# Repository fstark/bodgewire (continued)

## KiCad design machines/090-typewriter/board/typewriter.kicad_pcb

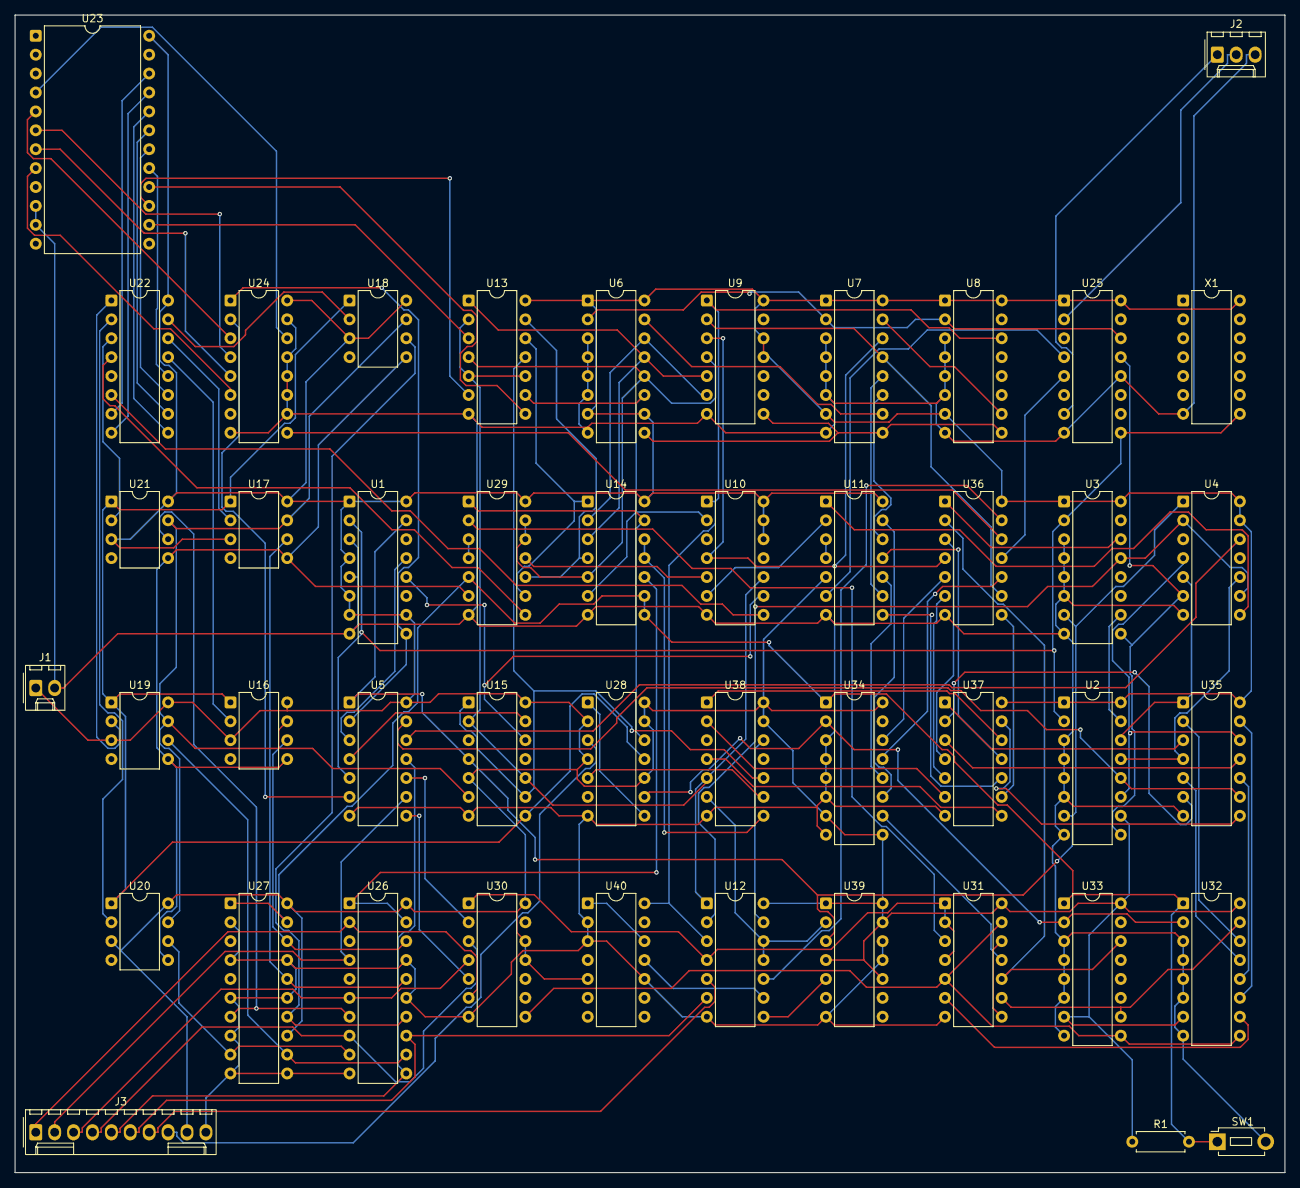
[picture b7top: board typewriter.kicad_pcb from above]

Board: 2 copper layers, 170.6 x 155.5 mm, 46 parts (0 on the bottom side), 127 nets.

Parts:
J1: POWER; Molex_KK-254_AE-6410-02A_1x02_P2.54mm_Vertical
J2: VIDEO; Molex_KK-254_AE-6410-03A_1x03_P2.54mm_Vertical
J3: KEYBOARD; Molex_KK-254_AE-6410-10A_1x10_P2.54mm_Vertical
R1: 4k7; R_Axial_DIN0207_L6.3mm_D2.5mm_P7.62mm_Horizontal
SW1: BUTTON; SW_PUSH_1P1T_6x3.5mm_H5.0_APEM_MJTP1250
U1, U2, U3, U6, U7, U8, U32, U33, U34: 74LS161; DIP-16_W7.62mm
U4, U10, U15, U38: 74LS20; DIP-14_W7.62mm
U5: 74LS04; DIP-14_W7.62mm
U9, U30: 74LS30; DIP-14_W7.62mm
U11, U35, U36: 74LS86; DIP-14_W7.62mm
U12, U14: 74LS02; DIP-14_W7.62mm
U13: 74LS08; DIP-14_W7.62mm
U16, U17, U18, U19, U20, U21: 2524; DIP-8_W7.62mm
U22: 2518; DIP-16_W7.62mm
U23: 2513; DIP-24_W15.24mm
U24: 74LS165; DIP-16_W7.62mm
U25: 74LS175; DIP-16_W7.62mm
U26, U27: 74LS244; DIP-20_W7.62mm
U28, U39: 74LS74; DIP-14_W7.62mm
U29, U31: 74LS00; DIP-14_W7.62mm
U37: 74LS27; DIP-14_W7.62mm
U40: 74LS93; DIP-14_W7.62mm
X1: OSC; DIP-14_W7.62mm

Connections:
ACTIVE: U10.10 (2B), U12.1 (1Y), U13.2 (1B), U13.5 (2B), U13.10 (3B), U15.2 (1B), U15.10 (2B), U38.5 (1D)
ADV: U31.6 (2Y), U32.10 (ENT)
B0: U22.12 (OUT1), U23.17 (A4)
B1: U22.11 (OUT2), U23.18 (A5)
B2: U22.10 (OUT3), U23.19 (A6)
B3: U22.9 (OUT4), U23.20 (A7)
B4: U22.8 (OUT5), U23.21 (A8)
B5: U22.7 (OUT6), U23.22 (A9)
BLINK: U12.9 (3B), U40.11 (QD)
C0: U2.14 (QA), U4.5 (1D), U35.1 (1A)
C1: U2.13 (QB), U4.10 (2B), U35.4 (2A)
C2: U2.12 (QC), U5.13 (6A), U35.9 (3A)
C2_N: U4.12 (2C), U5.12
C3: U2.11 (QD), U4.4 (1C), U35.12 (4A)
C4: U3.14 (QA), U36.1 (1A)
C5: U3.13 (QB), U4.2 (1B), U4.9 (2A), U12.2 (1A)
CC: U2.15 (RCO), U3.10 (ENT)
CLEAR: U14.10 (3Y), U26.1 (1OE_N), U26.19 (2OE_N)
CLEAR_N: R1.2, SW1.1, U14.8 (3A), U14.9 (3B), U27.1 (1OE_N), U27.19 (2OE_N), U29.5 (2B), U32.1 (CLR_N), U33.1 (CLR_N), U34.1 (CLR_N)
CLK: U1.2 (CLK), U2.2 (CLK), U3.2 (CLK), U5.5 (3A), U25.9 (CLK), X1.8 (OUT)
CLK_N: U5.6 (3Y), U24.2 (CLK)
CR_N: U30.8 (Y), U31.5 (2B), U31.13 (4B), U32.9 (LOAD_N), U33.9 (LOAD_N)
CTL: U12.4 (2Y), U30.1 (A), U31.1 (1A), U31.2 (1B), U31.4 (2A)
CURSOR_N: U12.8 (3A), U39.5 (1Q)
CUR_SHOW: U12.10 (3Y), U36.13 (4B)
D0: J3.1 (D0), U26.2 (1A1), U30.6 (F)
D1: J3.2 (D1), U5.9 (4A), U26.4 (1A2)
D1_N: U5.8 (4Y), U30.5 (E)
D2: J3.3 (D2), U26.6 (1A3), U30.4 (D)
D3: J3.4 (D3), U26.8 (1A4), U30.3 (C)
D4: J3.5 (D4), U5.11 (5A), U26.11 (2A1)
D4_N: U5.10 (5Y), U30.2 (B)
D5: J3.6 (D5), U12.6 (2B), U26.13 (2A2)
D6: J3.7 (D6), U12.5 (2A)
DOT_END: U1.15 (RCO), U2.7 (ENP), U3.7 (ENP), U4.1 (1A), U5.1 (1A), U15.4 (1C), U39.3 (1CLK)
DOT_LOAD_N: U1.9 (LOAD_N), U5.2 (1Y), U24.1 (SH_LD_N)
EQ0: U37.12 (1Y), U38.1 (1A)
EQ1: U37.6 (2Y), U38.2 (1B)
EQ2: U37.8 (3Y), U38.4 (1C)
F1: U23.4 (O1), U24.14 (D)
F2: U23.5 (O2), U24.3 (E)
F3: U23.6 (O3), U24.4 (F)
F4: U23.7 (O4), U24.5 (G)
F5: U23.8 (O5), U24.6 (H)
FRAME2: U40.1 (CKB), U40.12 (QA)
FRAME_END_N: U6.9 (LOAD_N), U7.9 (LOAD_N), U8.9 (LOAD_N), U9.8 (Y)
GL1: U13.3 (1Y), U23.14 (A1)
GL2: U13.6 (2Y), U23.15 (A2)
GL3: U13.8 (3Y), U23.16 (A3)
GND: J1.2 (GND), J2.3 (GND), J3.10 (GND), SW1.2, U1.3 (A), U1.5 (C), U1.8 (GND), U2.3 (A), U2.4 (B), U2.5 (C), U2.6 (D), U2.8 (GND), U3.3 (A), U3.4 (B), U3.5 (C), U3.6 (D), U3.8 (GND), U4.7 (GND), U5.7 (GND), U6.3 (A), U6.4 (B), U6.5 (C), U6.6 (D), U6.8 (GND), U7.3 (A), U7.4 (B), U7.5 (C), U7.6 (D), U7.8 (GND), U8.3 (A), U8.4 (B), U8.5 (C), U8.6 (D), U8.8 (GND), U9.7 (GND), U10.7 (GND), U11.7 (GND), U12.7 (GND), U13.7 (GND), U14.7 (GND), U15.7 (GND), U23.10 (GND), U23.11 (CE_N), U24.8 (GND), U24.10 (SER), U24.11 (A), U24.12 (B), U24.13 (C), U24.15 (CLK_INH), U25.8 (GND), U25.12 (3D), U26.10 (GND), U26.15 (2A3), U26.17 (2A4), U27.2 (1A1), U27.4 (1A2), U27.6 (1A3), U27.8 (1A4), U27.10 (GND), U27.11 (2A1), U27.15 (2A3), U27.17 (2A4), U28.7 (GND), U29.7 (GND), U30.7 (GND), U31.7 (GND), U32.3 (A), U32.4 (B), U32.5 (C), U32.6 (D), U32.8 (GND), U33.3 (A), U33.4 (B), U33.5 (C), U33.6 (D), U33.8 (GND), U34.3 (A), U34.4 (B), U34.5 (C), U34.6 (D), U34.8 (GND), U35.7 (GND), U36.7 (GND), U37.7 (GND), U38.7 (GND), U39.7 (GND), U39.11 (2CLK), U39.12 (2D), U40.2 (R01), U40.3 (R02), U40.10 (GND), X1.7 (GND)
GO: U14.13 (4Y), U28.12 (2D), U29.1 (1A)
GO_N: U14.11 (4A), U14.12 (4B), U38.8 (2Y)
HSYNC_N: U4.8 (2Y), U11.1 (1A)
KEY: U28.5 (1Q), U38.9 (2A)
LINE_END: U6.2 (CLK), U7.2 (CLK), U8.2 (CLK), U25.14 (4Q_N)
LINE_END_N: U2.9 (LOAD_N), U3.9 (LOAD_N), U4.6 (1Y), U25.13 (4D)
MATCH: U12.13 (4Y), U38.12 (2C)
MATCH_N: U12.11 (4A), U12.12 (4B), U38.6 (1Y), U39.2 (1D)
NE0: U35.3 (1Y), U37.1 (1A)
NE1: U35.6 (2Y), U37.2 (1B)
NE2: U35.8 (3Y), U37.13 (1C)
NE3: U35.11 (4Y), U37.3 (2A)
NE4: U36.3 (1Y), U37.4 (2B)
NE5: U36.6 (2Y), U37.5 (2C)
NE6: U36.8 (3Y), U37.9 (3A)
NE7: U11.8 (3Y), U37.10 (3B)
NE8: U11.11 (4Y), U37.11 (3C)
P0: U16.2 (OUT), U22.13 (IN1)
P1: U17.2 (OUT), U22.14 (IN2)
P2: U18.2 (OUT), U22.15 (IN3)
P3: U19.2 (OUT), U22.1 (IN4)
P4: U20.2 (OUT), U22.2 (IN5)
P5: U21.2 (OUT), U22.3 (IN6)
PHI1_N: U15.6 (1Y), U16.7 (PHI1), U17.7 (PHI1), U18.7 (PHI1), U19.7 (PHI1), U20.7 (PHI1), U21.7 (PHI1)
PHI2_N: U15.8 (2Y), U16.1 (PHI2), U17.1 (PHI2), U18.1 (PHI2), U19.1 (PHI2), U20.1 (PHI2), U21.1 (PHI2), U28.11 (2CLK)
PRINT: U29.2 (1B), U31.3 (1Y)
QB: U1.13 (QB), U5.3 (2A)
QB_N: U5.4 (2Y), U15.13 (2D)
QC: U1.12 (QC), U10.9 (2A), U15.12 (2C)
ROW_CLK: U10.8 (2Y), U22.6 (CLK)
ROW_LOAD_N: U22.4 (REC), U29.8 (3Y)
ROW_TOP: U13.11 (4Y), U15.1 (1A), U15.9 (2A), U38.10 (2B)
STROBE: J3.8 (STROBE), U28.3 (1CLK)
SYNC: U11.3 (1Y), U11.4 (2A)
SYNC_N: J2.2 (SYNC_N), U25.2 (1Q)
SYNC_N_D: U11.6 (2Y), U25.4 (1D)
V0: U6.14 (QA), U9.6 (F), U14.2 (1A)
V1: U6.13 (QB), U9.5 (E), U13.1 (1A), U14.3 (1B)
V01_ZERO: U13.12 (4A), U14.1 (1Y), U29.9 (3A)
V2: U6.12 (QC), U9.4 (D), U13.4 (2A), U14.5 (2A), U29.12 (4A), U29.13 (4B)
V2_N: U10.5 (1D), U29.11
V3: U6.11 (QD), U10.2 (1B), U13.9 (3A), U14.6 (2B)
V4: U7.14 (QA), U9.3 (C), U10.4 (1C), U36.4 (2A)
V5: U7.13 (QB), U9.2 (B), U36.9 (3A)
V6: U7.12 (QC), U11.9 (3A)
V7: U7.11 (QD), U11.12 (4A)
V8: U8.14 (QA), U9.1 (A), U10.1 (1A), U12.3 (1B), U40.14 (CKA)
V23_ZERO: U13.13 (4B), U14.4 (2Y), U29.10 (3B)
VC1: U6.15 (RCO), U7.10 (ENT)
VC2: U7.15 (RCO), U8.10 (ENT)
VCC: J1.1 (VCC), J3.9 (VCC), R1.1, U1.1 (CLR_N), U1.4 (B), U1.6 (D), U1.7 (ENP), U1.10 (ENT), U1.16 (VCC), U2.1 (CLR_N), U2.10 (ENT), U2.16 (VCC), U3.1 (CLR_N), U3.16 (VCC), U4.13 (2D), U4.14 (VCC), U5.14 (VCC), U6.1 (CLR_N), U6.7 (ENP), U6.10 (ENT), U6.16 (VCC), U7.1 (CLR_N), U7.7 (ENP), U7.16 (VCC), U8.1 (CLR_N), U8.7 (ENP), U8.16 (VCC), U9.11 (G), U9.12 (H), U9.14 (VCC), U10.12 (2C), U10.13 (2D), U10.14 (VCC), U11.5 (2B), U11.14 (VCC), U12.14 (VCC), U13.14 (VCC), U14.14 (VCC), U15.5 (1D), U15.14 (VCC), U16.3 (READ), U16.8 (VCC), U17.3 (READ), U17.8 (VCC), U18.3 (READ), U18.8 (VCC), U19.3 (READ), U19.8 (VCC), U20.3 (READ), U20.8 (VCC), U21.3 (READ), U21.8 (VCC), U22.16 (VCC), U23.24 (VCC), U24.16 (VCC), U25.1 (CLR_N), U25.16 (VCC), U26.20 (VCC), U27.13 (2A2), U27.20 (VCC), U28.2 (1D), U28.4 (1PRE_N), U28.10 (2PRE_N), U28.13 (2CLR_N), U28.14 (VCC), U29.14 (VCC), U30.11 (G), U30.12 (H), U30.14 (VCC), U31.14 (VCC), U32.7 (ENP), U32.16 (VCC), U33.7 (ENP), U33.16 (VCC), U34.7 (ENP), U34.9 (LOAD_N), U34.16 (VCC), U35.14 (VCC), U36.14 (VCC), U37.14 (VCC), U38.13 (2D), U38.14 (VCC), U39.1 (1CLR_N), U39.4 (1PRE_N), U39.10 (2PRE_N), U39.13 (2CLR_N), U39.14 (VCC), U40.5 (VCC), X1.14 (VCC)
VIDEO: J2.1 (VIDEO), U25.7 (2Q)
VIDEO_D: U24.9 (QH), U36.12 (4A)
VIDEO_M: U25.5 (2D), U36.11 (4Y)
VSYNC_N: U10.6 (1Y), U11.2 (1B)
W0: U16.6 (IN), U26.18 (1Y1), U27.18 (1Y1)
W1: U17.6 (IN), U26.16 (1Y2), U27.16 (1Y2)
W2: U18.6 (IN), U26.14 (1Y3), U27.14 (1Y3)
W3: U19.6 (IN), U26.12 (1Y4), U27.12 (1Y4)
W4: U20.6 (IN), U26.9 (2Y1), U27.9 (2Y1)
W5: U21.6 (IN), U26.7 (2Y2), U27.7 (2Y2)
WR: U28.9 (2Q), U32.2 (CLK), U33.2 (CLK), U34.2 (CLK)
WRITE: U16.5 (WRITE), U17.5 (WRITE), U18.5 (WRITE), U19.5 (WRITE), U20.5 (WRITE), U21.5 (WRITE), U29.6 (2Y)
WRK_N: U29.3 (1Y), U29.4 (2A)
WR_N: U28.1 (1CLR_N), U28.8 (2Q_N)
X0: U32.14 (QA), U35.2 (1B)
X1: U32.13 (QB), U35.5 (2B)
X2: U32.12 (QC), U35.10 (3B)
X3: U32.11 (QD), U35.13 (4B)
X4: U31.10 (3B), U33.14 (QA), U36.2 (1B)
XC_N: U31.8 (3Y), U31.12 (4A)
XRCO: U31.9 (3A), U32.15 (RCO), U33.10 (ENT)
Y0: U34.14 (QA), U36.5 (2B)
Y1: U34.13 (QB), U36.10 (3B)
Y2: U11.10 (3B), U34.12 (QC)
Y3: U11.13 (4B), U34.11 (QD)
YEN: U31.11 (4Y), U34.10 (ENT)

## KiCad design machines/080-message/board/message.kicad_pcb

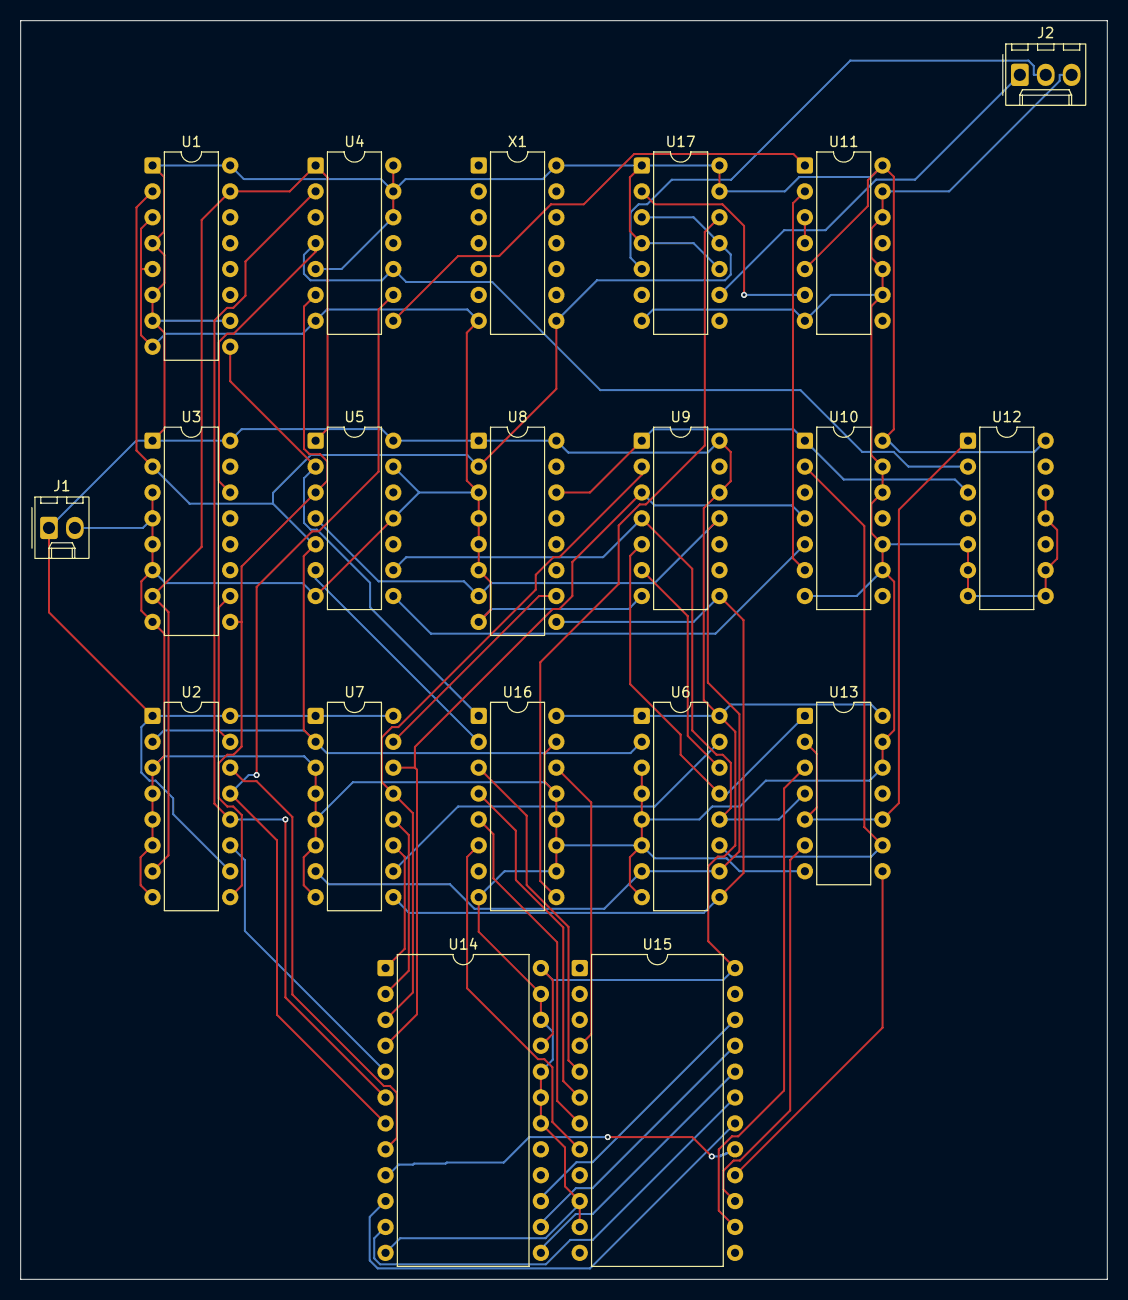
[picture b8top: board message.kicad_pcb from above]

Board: 2 copper layers, 106.6 x 123.5 mm, 20 parts (0 on the bottom side), 49 nets.

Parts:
J1: POWER; Molex_KK-254_AE-6410-02A_1x02_P2.54mm_Vertical
J2: VIDEO; Molex_KK-254_AE-6410-03A_1x03_P2.54mm_Vertical
U1, U2, U3, U6, U7, U8: 74LS161; DIP-16_W7.62mm
U4, U10: 74LS20; DIP-14_W7.62mm
U5: 74LS04; DIP-14_W7.62mm
U9: 74LS30; DIP-14_W7.62mm
U11: 74LS86; DIP-14_W7.62mm
U12: 74LS02; DIP-14_W7.62mm
U13: 74LS08; DIP-14_W7.62mm
U14: 2716; DIP-24_W15.24mm
U15: 2513; DIP-24_W15.24mm
U16: 74LS165; DIP-16_W7.62mm
U17: 74LS74; DIP-14_W7.62mm
X1: OSC; DIP-14_W7.62mm

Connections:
ACTIVE: U12.1 (1Y), U13.2 (1B), U13.5 (2B), U13.10 (3B)
C0: U2.14 (QA), U14.8 (A0)
C1: U2.13 (QB), U4.9 (2A), U14.7 (A1)
C2: U2.12 (QC), U4.2 (1B), U14.6 (A2)
C3: U2.11 (QD), U14.5 (A3)
C4: U3.14 (QA), U4.4 (1C), U4.10 (2B), U12.2 (1A)
CC: U2.15 (RCO), U3.10 (ENT)
CH0: U14.9 (O0), U15.17 (A4)
CH1: U14.10 (O1), U15.18 (A5)
CH2: U14.11 (O2), U15.19 (A6)
CH3: U14.13 (O3), U15.20 (A7)
CH4: U14.14 (O4), U15.21 (A8)
CH5: U14.15 (O5), U15.22 (A9)
CLK: U1.2 (CLK), U2.2 (CLK), U3.2 (CLK), U5.5 (3A), U6.2 (CLK), U7.2 (CLK), U8.2 (CLK), U17.3 (1CLK), U17.11 (2CLK), X1.8 (OUT)
CLK_N: U5.6 (3Y), U16.2 (CLK)
DOT_END: U1.15 (RCO), U2.7 (ENP), U3.7 (ENP), U4.1 (1A), U5.1 (1A)
DOT_LOAD_N: U1.9 (LOAD_N), U5.2 (1Y), U16.1 (SH_LD_N)
F1: U15.4 (O1), U16.14 (D)
F2: U15.5 (O2), U16.3 (E)
F3: U15.6 (O3), U16.4 (F)
F4: U15.7 (O4), U16.5 (G)
F5: U15.8 (O5), U16.6 (H)
FRAME_END_N: U6.9 (LOAD_N), U7.9 (LOAD_N), U8.9 (LOAD_N), U9.8 (Y)
GND: J1.2 (GND), J2.3 (GND), U1.3 (A), U1.5 (C), U1.8 (GND), U2.3 (A), U2.4 (B), U2.5 (C), U2.6 (D), U2.8 (GND), U3.3 (A), U3.4 (B), U3.5 (C), U3.6 (D), U3.8 (GND), U4.7 (GND), U5.7 (GND), U5.11 (5A), U5.13 (6A), U6.3 (A), U6.4 (B), U6.5 (C), U6.6 (D), U6.8 (GND), U7.3 (A), U7.4 (B), U7.5 (C), U7.6 (D), U7.8 (GND), U8.3 (A), U8.4 (B), U8.5 (C), U8.6 (D), U8.8 (GND), U9.7 (GND), U10.7 (GND), U10.9 (2A), U10.10 (2B), U10.12 (2C), U10.13 (2D), U11.7 (GND), U11.9 (3A), U11.10 (3B), U11.12 (4A), U11.13 (4B), U12.5 (2A), U12.6 (2B), U12.7 (GND), U12.8 (3A), U12.9 (3B), U12.11 (4A), U12.12 (4B), U13.7 (GND), U13.12 (4A), U13.13 (4B), U14.12 (GND), U14.18 (CE_N), U14.19 (A10), U14.20 (OE_N), U14.22 (A9), U14.23 (A8), U15.10 (GND), U15.11 (CE_N), U16.8 (GND), U16.10 (SER), U16.11 (A), U16.12 (B), U16.13 (C), U16.15 (CLK_INH), U17.7 (GND), X1.7 (GND)
HSYNC_N: U4.8 (2Y), U11.1 (1A)
LINE_END: U5.4 (2Y), U6.7 (ENP), U6.10 (ENT), U7.7 (ENP), U8.7 (ENP), U9.11 (G)
LINE_END_N: U2.9 (LOAD_N), U3.9 (LOAD_N), U4.6 (1Y), U5.3 (2A)
R1: U13.3 (1Y), U15.14 (A1)
R2: U13.6 (2Y), U15.15 (A2)
R3: U13.8 (3Y), U15.16 (A3)
SYNC: U11.3 (1Y), U11.4 (2A)
SYNC_N: J2.2 (SYNC_N), U17.5 (1Q)
SYNC_N_D: U11.6 (2Y), U17.2 (1D)
V0: U6.14 (QA), U9.6 (F)
V1: U6.13 (QB), U9.5 (E), U13.1 (1A)
V2: U5.9 (4A), U6.12 (QC), U9.4 (D), U13.4 (2A)
V2_N: U5.8, U10.5 (1D)
V3: U6.11 (QD), U10.2 (1B), U13.9 (3A)
V4: U7.14 (QA), U9.3 (C), U10.4 (1C), U14.4 (A4)
V5: U7.13 (QB), U9.2 (B), U14.3 (A5)
V6: U7.12 (QC), U14.2 (A6)
V7: U7.11 (QD), U14.1 (A7)
V8: U8.14 (QA), U9.1 (A), U10.1 (1A), U12.3 (1B)
VC1: U6.15 (RCO), U7.10 (ENT)
VC2: U7.15 (RCO), U8.10 (ENT)
VCC: J1.1 (VCC), U1.1 (CLR_N), U1.4 (B), U1.6 (D), U1.7 (ENP), U1.10 (ENT), U1.16 (VCC), U2.1 (CLR_N), U2.10 (ENT), U2.16 (VCC), U3.1 (CLR_N), U3.16 (VCC), U4.5 (1D), U4.12 (2C), U4.13 (2D), U4.14 (VCC), U5.14 (VCC), U6.1 (CLR_N), U6.16 (VCC), U7.1 (CLR_N), U7.16 (VCC), U8.1 (CLR_N), U8.16 (VCC), U9.12 (H), U9.14 (VCC), U10.14 (VCC), U11.5 (2B), U11.14 (VCC), U12.14 (VCC), U13.14 (VCC), U14.21 (VPP), U14.24 (VCC), U15.24 (VCC), U16.16 (VCC), U17.1 (1CLR_N), U17.4 (1PRE_N), U17.10 (2PRE_N), U17.13 (2CLR_N), U17.14 (VCC), X1.14 (VCC)
VIDEO: J2.1 (VIDEO), U17.9 (2Q)
VIDEO_D: U16.9 (QH), U17.12 (2D)
VSYNC_N: U10.6 (1Y), U11.2 (1B)

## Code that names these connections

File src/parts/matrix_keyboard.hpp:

#pragma once

#include <array>
#include <atomic>
#include <cstddef>
#include <cstdint>
#include <optional>
#include <span>
#include <string>
#include <string_view>
#include <vector>

#include "parts/key_matrix.hpp"
#include "parts/press_queue.hpp"
#include "parts/switch.hpp"
#include "sim/component.hpp"
#include "sim/time.hpp"

namespace bw {

// One key of the BW-2001 keyboard: where it is in the matrix and what its cap says.
struct MatrixKey {
    std::uint8_t row;          // 0-9: the 74LS145 output that scans it
    std::uint8_t column;       // 0-7: PIA1 PB0-PB7
    std::string_view legend;   // "A", "RETURN", "CRSR RT"
    std::string_view shifted;  // "" or what SHIFT makes of it ("CLR", "INST", "CRSR LF", "CRSR UP")
};

// The PET 2001's 73 keys (P5p's matrix, BW2001_FIRMWARE.md), row 0 column 0 first; the index of
// a key in this span is its index everywhere (setHeld, MatrixPress).
std::span<const MatrixKey> Bw2001Keys();
std::optional<std::size_t> Bw2001KeyAt(int row, int column);
inline constexpr std::size_t kBw2001KeyCount = 73;

// The press that types `c` on the BW-2001 keyboard: 0x20-0x5F by the key whose legend it is ('_'
// the left-arrow key, '^' the up-arrow key), a-z as A-Z, '\n' or '\r' RETURN, '\b' or kKeyDel
// DEL, the kKey… named keys (CLR, INST, CRSR LF, CRSR UP with SHIFT); nullopt for anything else.
std::optional<MatrixPress> MatrixKeyFor(char32_t c);

// The BW-2001 keyboard behind a BW2001KB connector (P5q): a 10 x 8 key matrix and nothing else.
// Pins 1-10 ROW0-ROW9, 11-18 COL0-COL7, 19-20 not connected (pin index = pad - 1). Each key is a
// SwitchContact between its row and column Pins' Nets, joined by the Board's switch network as a
// switch's legs. Held from outside (setHeld) or typed in simulation time (type); no Faults.
class MatrixKeyboard final : public Component, public KeyMatrix {
public:
    explicit MatrixKeyboard(std::string reference);
    static constexpr PinIndex kRow0 = 0, kColumn0 = 10;

    // The builder's: each key a contact between its row Pin and its column Pin, joined by the
    // Board's switch network.
    SwitchContact& contact(std::size_t key) { return contacts_[key]; }
    std::array<PinIndex, 2> contactPins(std::size_t key) const {
        const MatrixKey& k = Bw2001Keys()[key];
        return {static_cast<PinIndex>(kRow0 + k.row), static_cast<PinIndex>(kColumn0 + k.column)};
    }

    KeyMatrixKind kind() const override { return KeyMatrixKind::Bw2001; }
    std::size_t keyCount() const override { return kBw2001KeyCount; }
    std::size_t shiftKey() const override;  // the left SHIFT: row 8, column 0
    Component& component() override { return *this; }
    void setHeld(std::size_t key, bool held) override { held_[key] = held; }
    bool held(std::size_t key) const override { return held_[key]; }
    // Each character through MatrixKeyFor; false when none was queued.
    bool type(std::u32string_view text) override;
    // One character; false (nothing queued) when `c` has no key or kMatrixWaiting presses wait.
    bool type(char32_t c);
    bool press(MatrixPress press) override { return press.key < keyCount() && queue_.push(press); }
    void dropWaiting() override { queue_.dropWaiting(); }
    bool scripted(std::size_t key) const override { return queue_.scripted(key, shiftKey()); }

    void powerOn(PowerOnContext& ctx) override;  // contacts open, Idle; waiting presses kept
    void evaluate(EvalContext& ctx) override;

private:
    std::vector<SwitchContact> contacts_;
    std::array<bool, kBw2001KeyCount> held_{};
    PressQueue queue_{kMatrixHold, kMatrixGap};
};

}  // namespace bw

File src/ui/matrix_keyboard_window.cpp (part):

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constexpr float kMargin = 0.55f;  // the bezel around the keys
constexpr float kLabel = 0.40f;   // the name strip above the keys
constexpr float kInset = 0.10f;   // the case inside the window
constexpr float kGap = 0.06f;     // between the PET's keys: a grid, nearly touching
constexpr float kMinWidth = 380;

// The BW-80's case (P6l): the ZX80's cream lip around the black membrane, the membrane's black
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constexpr ImU32 kPetBlue = IM_COL32(36, 158, 218, 255);
constexpr ImU32 kPetWord = IM_COL32(248, 244, 244, 255);
constexpr ImU32 kLegend = IM_COL32(22, 22, 24, 255);
constexpr ImU32 kPetCellLine = IM_COL32(22, 22, 24, 90);  // the thin square around a graphic
constexpr ImU32 kPressed = IM_COL32(0, 0, 0, 48);

// An arrow centred on `c`, `len` long, its heads `head` wide; `vertical` or horizontal; heads at
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
// A colour a fifth of the way to white: the light on the top of a foil label.
ImU32 Lighter(ImU32 c) {
    const auto mix = [&](int shift) {
        const int v = static_cast<int>((c >> shift) & 0xFF);
        return v + (255 - v) / 5;
    };
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        return;
    }
    // A graphic above, the legend below: an arrow for ← and ↑, a slashed zero on the pad.
    if (const auto* glyph = PetGraphicOf(legend)) {
        // Each pixel whole device pixels (half points on a Retina display), so the check is even.
        // As printed: about a sixth of the key (the user's close-ups).
        const float cell = std::max(1.0f, std::round(0.022f * u * density)) / density;
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using Glyph = std::array<std::uint8_t, 8>;

Glyph GraphicOf(std::string_view legend) {
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    constexpr Glyph kBottom{0, 0, 0, 0, 0xFF, 0xFF, 0xFF, 0xFF};                // W: 3
    constexpr Glyph kTopLeft{0xF0, 0xF0, 0xF0, 0xF0, 0, 0, 0, 0};               // E: 4
    constexpr Glyph kTopRight{0x0F, 0x0F, 0x0F, 0x0F, 0, 0, 0, 0};              // R: 5
    constexpr Glyph kBottomLeft{0, 0, 0, 0, 0xF0, 0xF0, 0xF0, 0xF0};            // D: 6
    constexpr Glyph kBottomRight{0, 0, 0, 0, 0x0F, 0x0F, 0x0F, 0x0F};           // F: 7
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    constexpr Glyph kGreyBottom{0, 0, 0, 0, 0xAA, 0x55, 0xAA, 0x55};            // T: 10
    constexpr Glyph kGreyTop{0xAA, 0x55, 0xAA, 0x55, 0, 0, 0, 0};               // G: 11
    if (legend == "Q")
        return kLeft;
    if (legend == "W")
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    list.AddRectFilled({x0 - frame, y0 - frame}, {x0 + 8 * cell + frame, y0 + 8 * cell + frame},
                       kGraphicFrame);
    list.AddRectFilled({x0, y0}, {x0 + 8 * cell, y0 + 8 * cell}, kKeyTop);
    const Glyph glyph = GraphicOf(legend);
    for (int y = 0; y < 8; ++y) {
        for (int x = 0; x < 8; ++x) {
            if ((glyph[y] >> (7 - x)) & 1) {
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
